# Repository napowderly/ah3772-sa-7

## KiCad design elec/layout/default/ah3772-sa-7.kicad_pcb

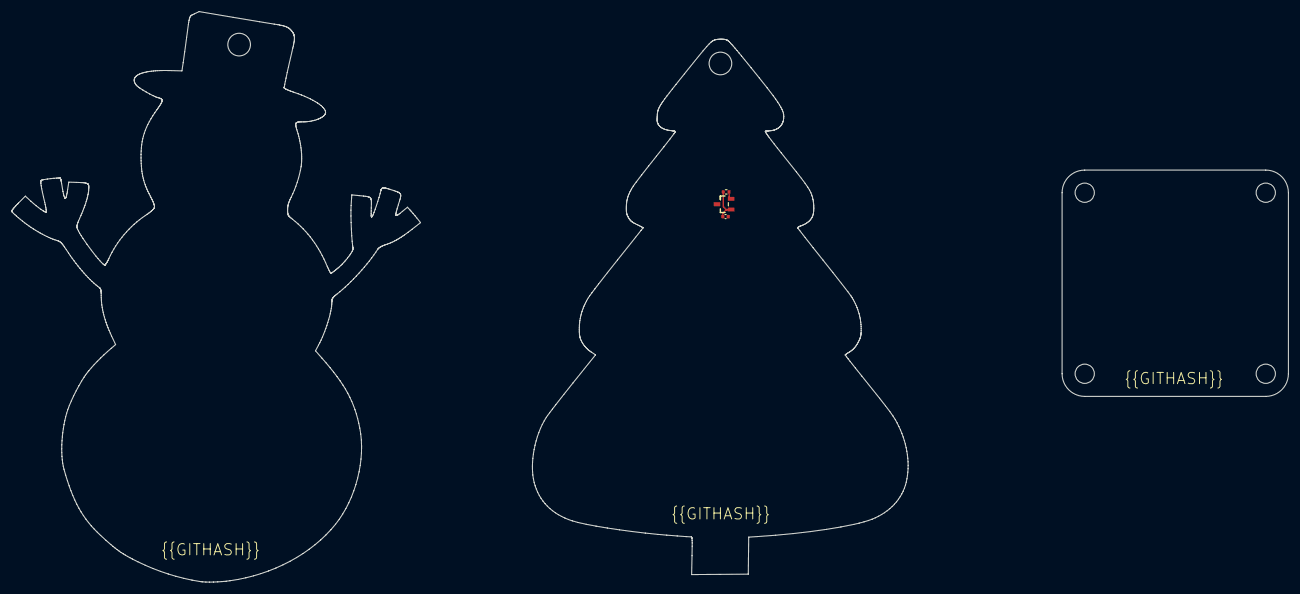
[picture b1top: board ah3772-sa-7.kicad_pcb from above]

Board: 2 copper layers, 66.4 x 94.6 mm, 3 parts (0 on the bottom side), 3 nets.

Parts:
C1: 16V 100nF X7R ±10% 0402 Multilayer Ceramic Capaci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; C0402
R1: 62.5mW Thick Film Resistors ±100ppm/℃ ±1% 1kΩ 040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; R0402
U1: SOT-23-3_L2.9-W1.3-P1.90-LS2.4-BR-CW

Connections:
gnd: C1.2, U1.2
out: R1.2, U1.3
vcc: C1.1, R1.1, U1.1

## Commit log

2024-02-17 Configure project
2024-02-17 layout
2024-03-08 update layout
